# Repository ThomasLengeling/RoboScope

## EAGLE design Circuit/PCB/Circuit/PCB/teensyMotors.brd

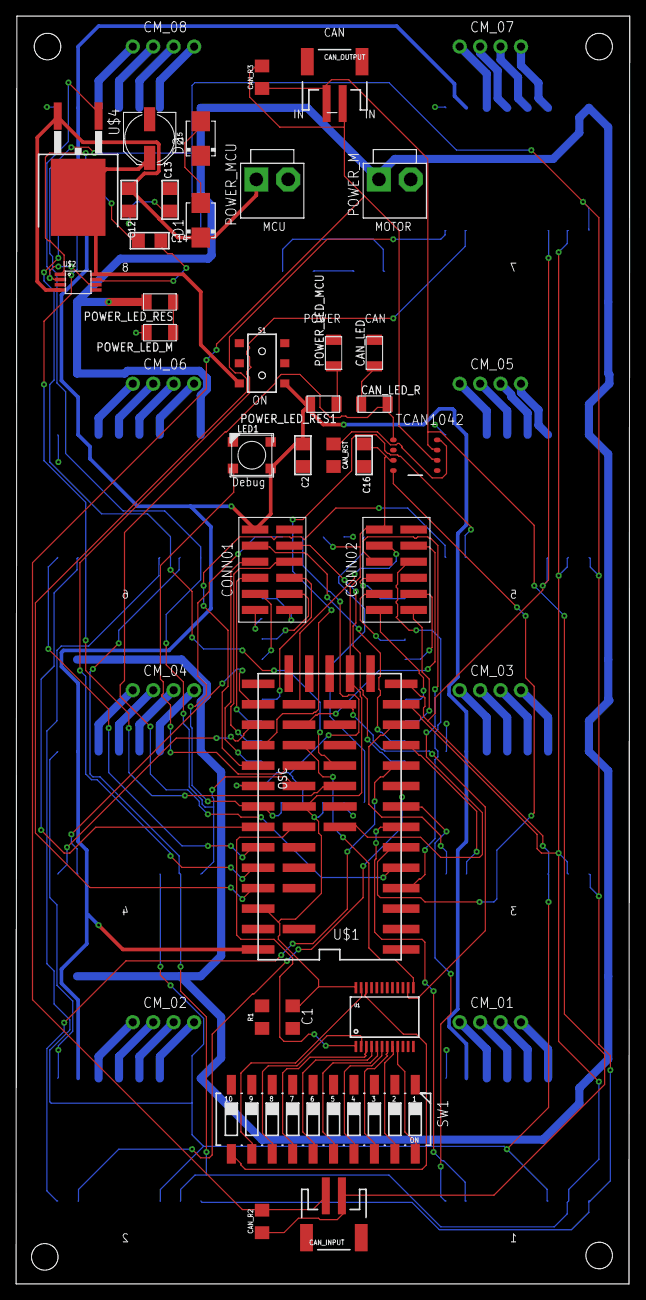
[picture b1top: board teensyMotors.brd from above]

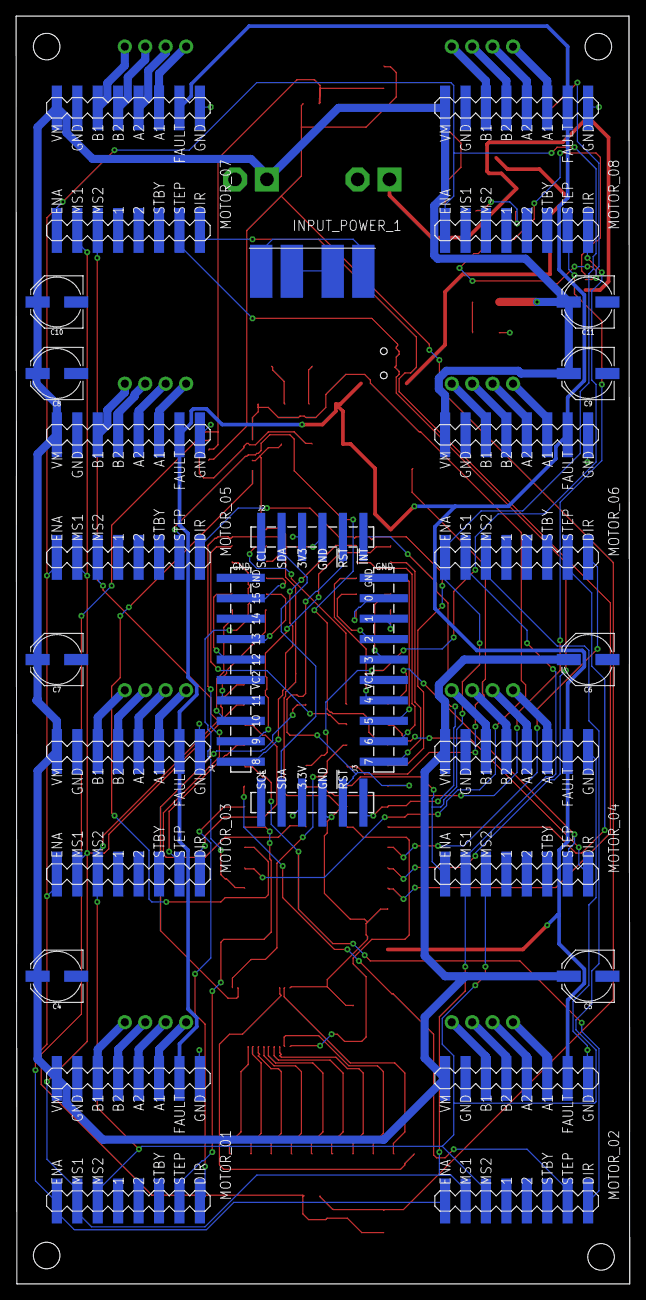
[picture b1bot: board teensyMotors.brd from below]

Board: 2 copper layers, 76.3 x 157.6 mm, 66 parts (21 on the bottom side), 109 nets.

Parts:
C1: 0.1uF; C1206
C2, C12, C13, C14, C16: 1206
C4, C5, C6, C7, C8, C9, C10, C11, C15: 100uF; PANASONIC_D
CAN_INPUT: JST-2-SMD
CAN_LED: LEDFAB1206; LED1206FAB
CAN_LED_R: 500; R1206FAB
CAN_OUTPUT: JST-2-SMD
CAN_R2, CAN_R3: 120ohm; 1206
CAN_RST: 10K; 1206
CM_01, CM_02, CM_03, CM_04, CM_05, CM_06, CM_07, CM_08: 1X04_SMD_STRAIGHT_COMBO; 1X04-CLEANBIG
CONN01, CONN02: TMMH-105-12
D1, D2: S2M; DO214AA
INPUT_POWER_1: MOLEX4015
J1, J2: 1X06_SMD_MALE
J3, J4: 1X10_SMD_MALE
LED1: LED5050_N
MOTOR_01, MOTOR_02, MOTOR_03, MOTOR_04, MOTOR_05, MOTOR_06, MOTOR_07, MOTOR_08: DRV8880
POWER_LED_M: LEDFAB1206; LED1206FAB
POWER_LED_MCU: LEDFAB1206; LED1206FAB
POWER_LED_RES, POWER_LED_RES1: 500; R1206FAB
POWER_M: B2P-VH
POWER_MCU: B2P-VH
R1: 1206
S1: SWITCH_DPDT_SMD_AYZ0202
STANDOFF5, STANDOFF6, STANDOFF7, STANDOFF8: STAND-OFF
SW1: 219-10; CTS-219-10
TCAN1042: Value; D0008A_N
U1: MUX-74HC4067; SSOP24
U$1: TEENSY_3.1-3.2_ALL_PINS&PADS_SMD; TEENSY_3.0-3.2_ALL_PINS_&_PADS_SMD
U$2: VSSOP(8)
U$4: TO263-3

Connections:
3.3V: C1.1, C16.1, CONN02.11, J1.4, J2.4, TCAN1042.3, U1.24, U$1.3.3V, U$1.3.3V1, U$1.3.3V2
C0: SW1.20, U1.9
C1: SW1.19, U1.8
C2: SW1.18, U1.7
C3: SW1.17, U1.6
C4: SW1.16, U1.5
C5: SW1.15, U1.4
C6: SW1.14, U1.3
C7: SW1.13, U1.2
C8: SW1.12, U1.23
C9: SW1.11, U1.22
CAN_H: CAN_INPUT.1, CAN_OUTPUT.1, CAN_R2.1, CAN_R3.1, TCAN1042.7
CAN_L: CAN_INPUT.2, CAN_OUTPUT.2, CAN_R2.2, CAN_R3.2, TCAN1042.6
CAN_RX: TCAN1042.4, U$1.4
CAN_TX: CAN_LED_R.2, TCAN1042.1, U$1.3
GND_IN: INPUT_POWER_1.GND_01, INPUT_POWER_1.GND_02
GND_M: C4.-, C5.-, C6.-, C7.-, C8.-, C9.-, C10.-, C11.-, MOTOR_01.GND_1, MOTOR_02.GND_1, MOTOR_03.GND_1, MOTOR_04.GND_1, MOTOR_05.GND_1, MOTOR_06.GND_1, MOTOR_07.GND_1, MOTOR_08.GND_1, POWER_LED_M.2, POWER_M.2
GND_MCU: C1.2, C2.2, C13.2, C15.-, C16.2, CAN_LED.2, CAN_RST.2, CONN01.12, CONN02.12, D2.C, J1.3, J2.3, LED1.3-GND, MOTOR_01.GND_0, MOTOR_02.GND_0, MOTOR_03.GND_0, MOTOR_04.GND_0, MOTOR_05.GND_0, MOTOR_06.GND_0, MOTOR_07.GND_0, MOTOR_08.GND_0, POWER_LED_MCU.2, POWER_MCU.2, R1.1, R1.2, SW1.1, SW1.2, SW1.3, SW1.4, SW1.5, SW1.6, SW1.7, SW1.8, SW1.9, SW1.10, TCAN1042.2, U1.12, U1.15, U$1.GND, U$1.GND1, U$1.GND2
I2CM_0: CONN01.1, J3.9
I2CM_1: CONN01.2, J3.8
I2CM_2: CONN01.3, J3.7
I2CM_3: CONN01.4, J3.6
I2CM_4: CONN01.5, J3.4
I2CM_5: CONN01.6, J3.3
I2CM_6: CONN01.7, J3.2
I2CM_7: CONN01.8, J3.1
I2CM_8: CONN01.9, J4.1
I2CM_9: CONN01.10, J4.2
I2CM_10: CONN02.1, J4.3
I2CM_11: CONN02.2, J4.4
I2CM_12: CONN02.3, J4.6
I2CM_13: CONN02.4, J4.7
I2CM_15: CONN02.6, J4.9
LED_DEBUG: LED1.4-DIN, U$1.32
MA1_01: CM_01.1, MOTOR_01.A1
MA1_02: CM_02.1, MOTOR_02.A1
MA1_03: CM_03.1, MOTOR_03.A1
MA1_04: CM_04.1, MOTOR_04.A1
MA1_05: CM_05.1, MOTOR_05.A1
MA1_06: CM_06.1, MOTOR_06.A1
MA1_07: CM_07.1, MOTOR_07.A1
MA1_08: CM_08.1, MOTOR_08.A1
MA2_01: CM_01.2, MOTOR_01.A2
MA2_02: CM_02.2, MOTOR_02.A2
MA2_03: CM_03.2, MOTOR_03.A2
MA2_04: CM_04.2, MOTOR_04.A2
MA2_05: CM_05.2, MOTOR_05.A2
MA2_06: CM_06.2, MOTOR_06.A2
MA2_07: CM_07.2, MOTOR_07.A2
MA2_08: CM_08.2, MOTOR_08.A2
MB1_01: CM_01.4, MOTOR_01.B1
MB1_02: CM_02.4, MOTOR_02.B1
MB1_03: CM_03.4, MOTOR_03.B1
MB1_04: CM_04.4, MOTOR_04.B1
MB1_05: CM_05.4, MOTOR_05.B1
MB1_06: CM_06.4, MOTOR_06.B1
MB1_07: CM_07.4, MOTOR_07.B1
MB1_08: CM_08.4, MOTOR_08.B1
MB2_01: CM_01.3, MOTOR_01.B2
MB2_02: CM_02.3, MOTOR_02.B2
MB2_03: CM_03.3, MOTOR_03.B2
MB2_04: CM_04.3, MOTOR_04.B2
MB2_05: CM_05.3, MOTOR_05.B2
MB2_06: CM_06.3, MOTOR_06.B2
MB2_07: CM_07.3, MOTOR_07.B2
MB2_08: CM_08.3, MOTOR_08.B2
MDIR_01: MOTOR_01.DIR, U$1.6
MDIR_02: MOTOR_02.DIR, U$1.8
MDIR_03: MOTOR_03.DIR, U$1.10
MDIR_04: MOTOR_04.DIR, U$1.15/A1
MDIR_05: MOTOR_05.DIR, U$1.17/A3
MDIR_06: MOTOR_06.DIR, U$1.21/A7
MDIR_07: MOTOR_07.DIR, U$1.23/A9
MDIR_08: MOTOR_08.DIR, U$1.25
MENABLE: MOTOR_01.ENA, MOTOR_02.ENA, MOTOR_03.ENA, MOTOR_04.ENA, MOTOR_05.ENA, MOTOR_06.ENA, MOTOR_07.ENA, MOTOR_08.ENA, U$1.33
MMS1: MOTOR_01.MS1, MOTOR_02.MS1, MOTOR_03.MS1, MOTOR_04.MS1, MOTOR_05.MS1, MOTOR_06.MS1, MOTOR_07.MS1, U$1.11
MMS2: MOTOR_01.MS2, MOTOR_02.MS2, MOTOR_03.MS2, MOTOR_04.MS2, MOTOR_05.MS2, MOTOR_06.MS2, MOTOR_07.MS2, U$1.12
MSTEP_01: MOTOR_01.STEP, U$1.5
MSTEP_02: MOTOR_02.STEP, U$1.7
MSTEP_03: MOTOR_03.STEP, U$1.9
MSTEP_04: MOTOR_04.STEP, U$1.14/A0
MSTEP_05: MOTOR_05.STEP, U$1.16/A2
MSTEP_06: MOTOR_06.STEP, U$1.20/A6
MSTEP_07: MOTOR_07.STEP, U$1.22/A8
MSTEP_08: MOTOR_08.STEP, U$1.24
MUX_RESET: J1.2, J2.2
MUX_S2: U1.14, U$1.28
MUX_S3: U1.13, U$1.31
MUX_SCL: J1.6, J2.6, U$1.19/A5
MUX_SDA: J1.5, J2.5, U$1.18/A4
MUX_SIG: U1.1, U$1.A13
unnamed: POWER_LED_M.1, POWER_LED_RES.1
unnamed: C14.2, U$2.VCAPH
unnamed: U$2.GDRIVE, U$2.GPD, U$4.1
unnamed: C14.1, U$2.VCAPL
unnamed: CAN_RST.1, TCAN1042.8
unnamed: POWER_LED_MCU.1, POWER_LED_RES1.1
unnamed: C12.2, C13.1
unnamed: D1.A, D2.A
unnamed: CAN_LED.1, CAN_LED_R.1
NEO_PIXEL: CONN02.7, U$1.2
REG_5V: C15.+, S1.6, U$2.CATHODE, U$4.4
S_SCL: CONN02.10, U$1.29
S_SDA: CONN02.9, U$1.30
S_SEN_01: CONN02.8, U$1.A12
VCC_5V: C2.1, CONN01.11, LED1.1-VDD, MOTOR_01.FAULT, MOTOR_02.FAULT, MOTOR_03.FAULT, MOTOR_04.FAULT, MOTOR_05.FAULT, MOTOR_06.FAULT, MOTOR_07.FAULT, MOTOR_08.FAULT, POWER_LED_RES1.2, S1.3, U$1.VIN
VCC_IN: INPUT_POWER_1.VCC_01, INPUT_POWER_1.VCC_02
VCC_M: C4.+, C5.+, C6.+, C7.+, C8.+, C9.+, C10.+, C11.+, MOTOR_01.VM, MOTOR_02.VM, MOTOR_03.VM, MOTOR_04.VM, MOTOR_05.VM, MOTOR_06.VM, MOTOR_07.VM, MOTOR_08.VM, POWER_LED_RES.2, POWER_M.1
VCC_MCU: C12.1, D1.C, POWER_MCU.1, U$2.ANODE, U$4.3

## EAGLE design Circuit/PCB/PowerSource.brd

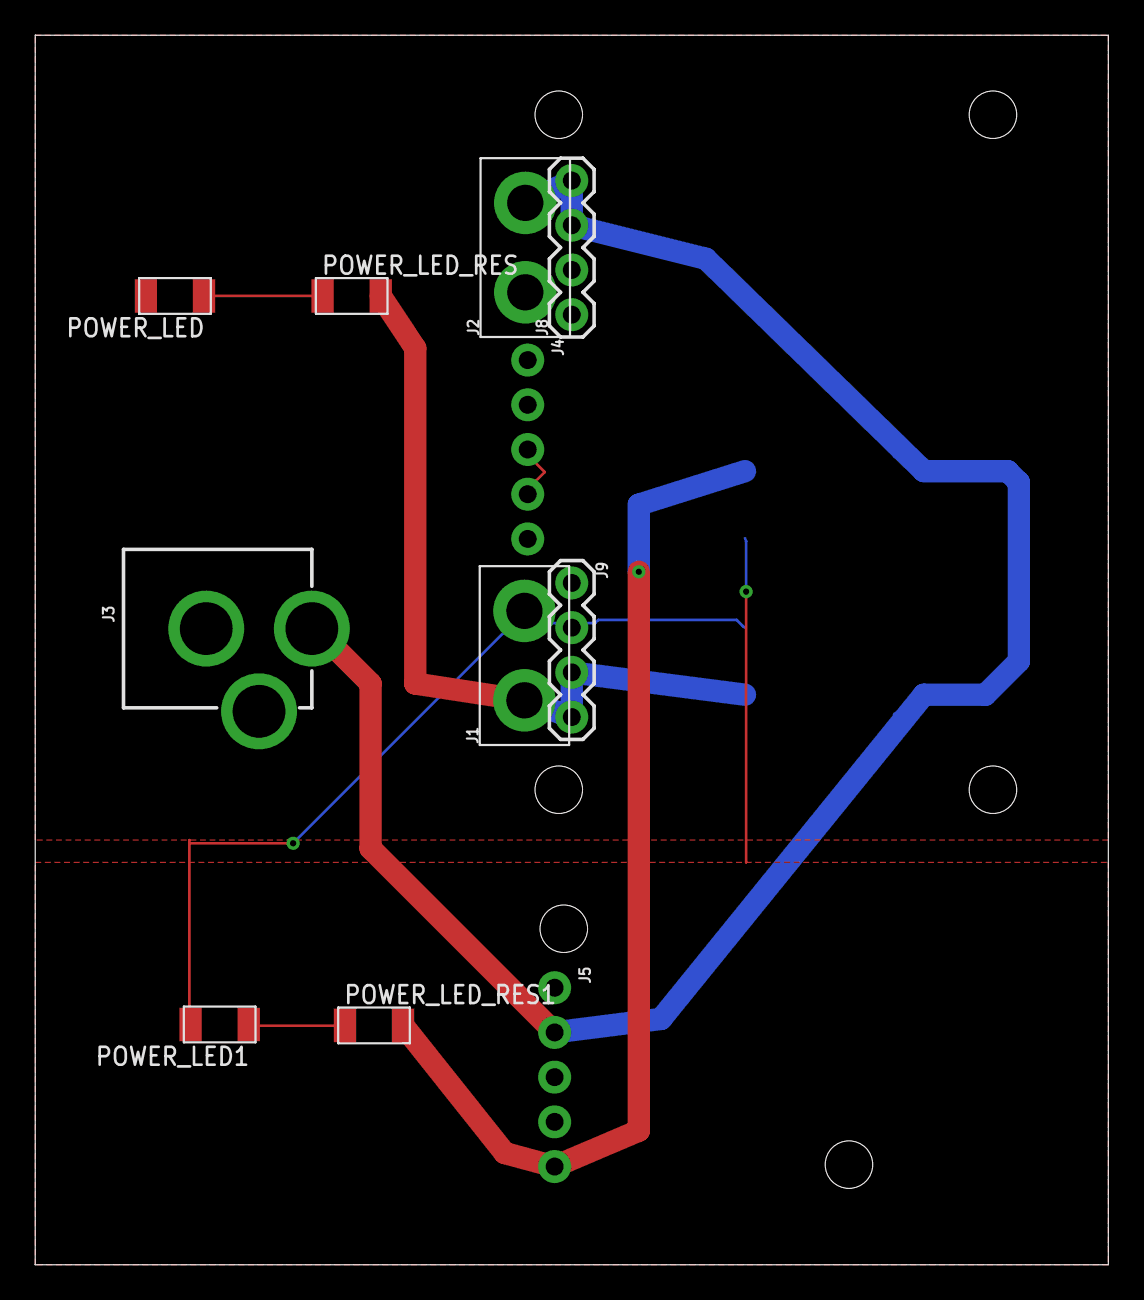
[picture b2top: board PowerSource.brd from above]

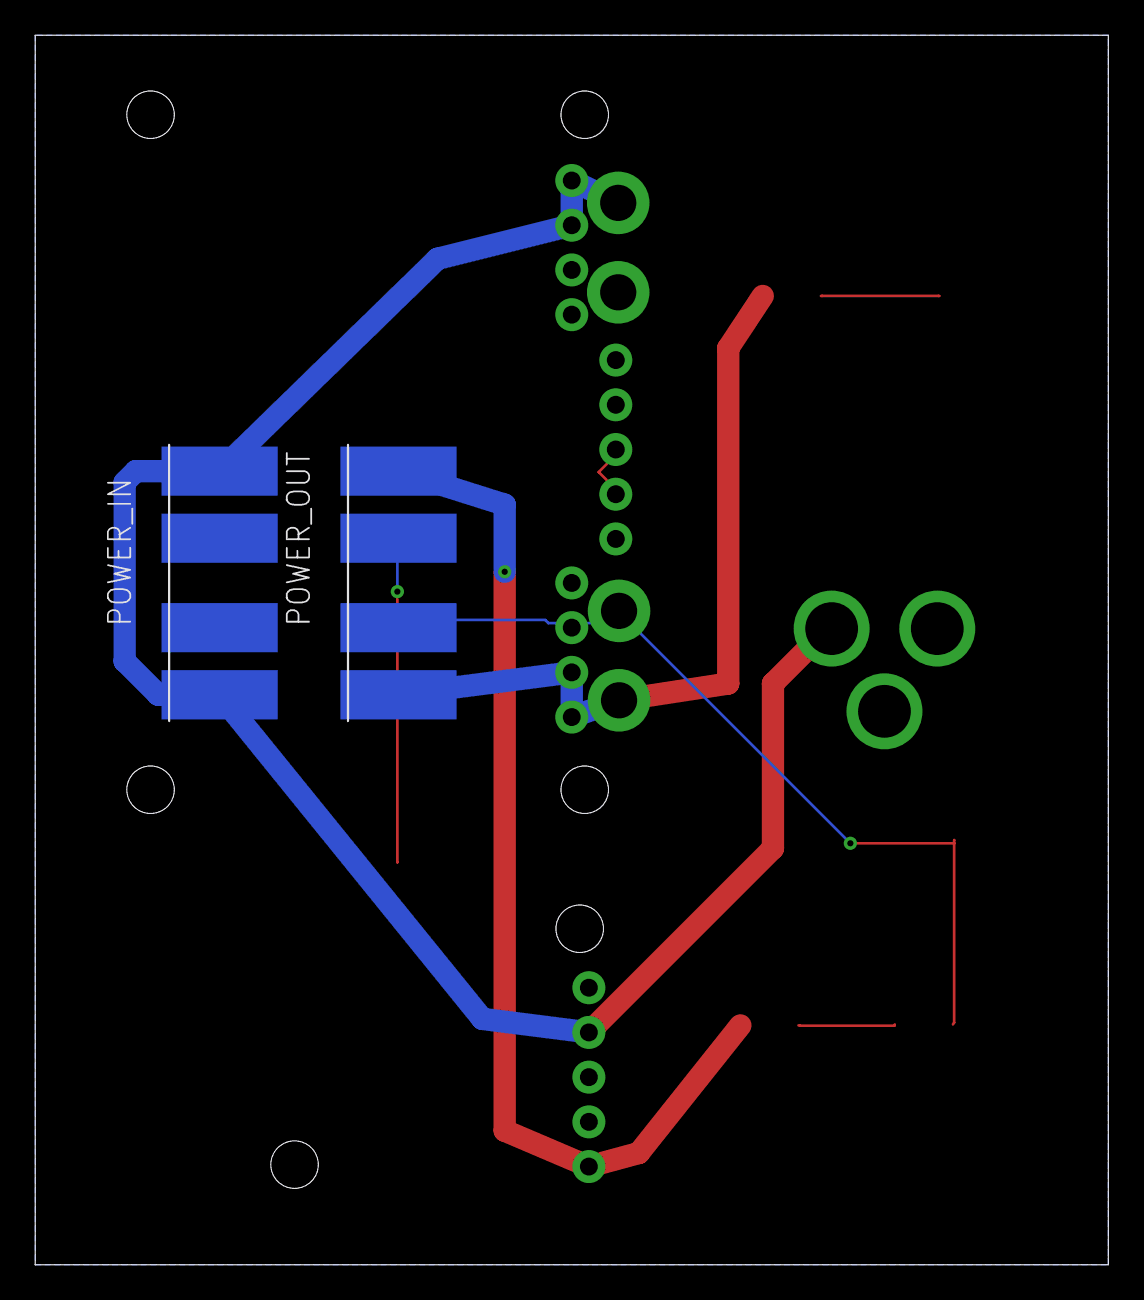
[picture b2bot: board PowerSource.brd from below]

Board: 2 copper layers, 61.0 x 69.8 mm, 13 parts (2 on the bottom side), 9 nets.

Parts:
J1, J2: 1X02_XTRA_BIG
J3: POWER_JACK; POWER_JACK_PTH
J4, J5: 1X05_NO_SILK
J8, J9: 1X04
POWER_IN: MOLEX4015
POWER_LED, POWER_LED1: LEDFAB1206; LED1206FAB
POWER_LED_RES, POWER_LED_RES1: 500; R1206FAB
POWER_OUT: MOLEX4015

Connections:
GND: J4.3, J4.4
GND_IN: J2.1, J3.GND, J3.GNDBREAK, J5.3, J8.1, J8.2, POWER_IN.GND_01, POWER_IN.GND_02
GND_M: J1.2, J9.1, J9.2, POWER_LED.2, POWER_LED1.2, POWER_OUT.GND_01
GND_MCU: J5.4, POWER_OUT.GND_02
unnamed: POWER_LED.1, POWER_LED_RES.1
unnamed: POWER_LED1.1, POWER_LED_RES1.1
VCC_IN: J2.2, J3.PWR, J5.2, J8.3, J8.4, POWER_IN.VCC_01, POWER_IN.VCC_02
VCC_M: J1.1, J9.3, J9.4, POWER_LED_RES.2, POWER_OUT.VCC_01
VCC_MCU: J5.5, POWER_LED_RES1.2, POWER_OUT.VCC_02

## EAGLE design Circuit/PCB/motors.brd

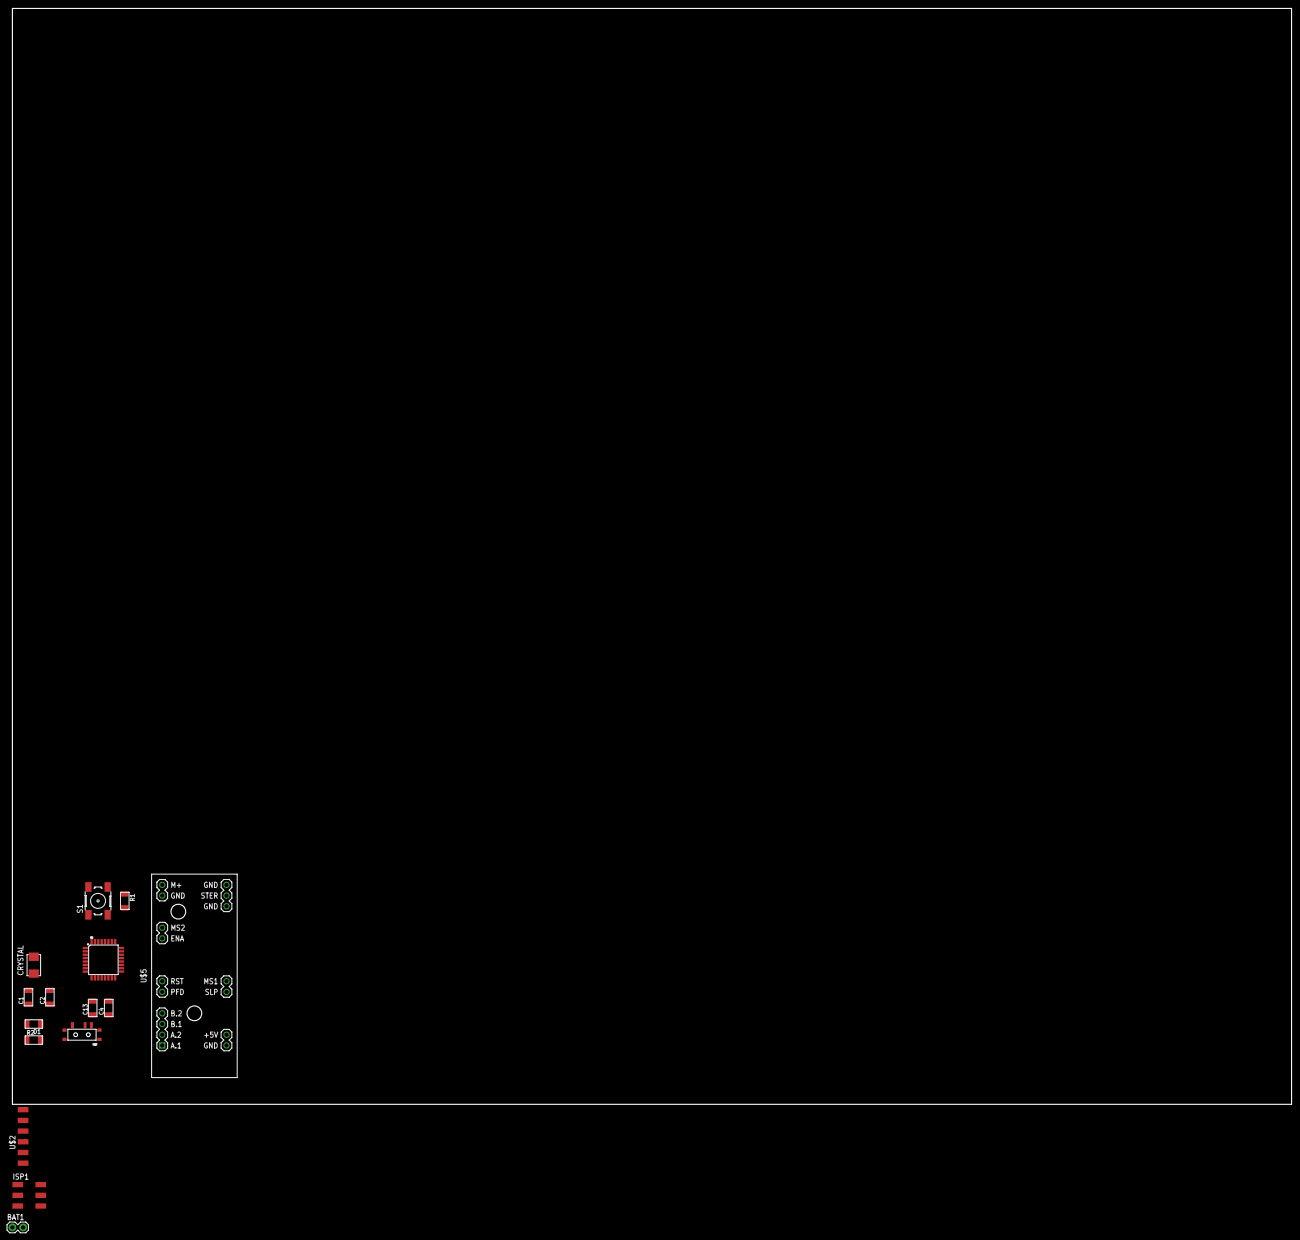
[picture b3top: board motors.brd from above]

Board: 2 copper layers, 303.5 x 260.0 mm, 15 parts (0 on the bottom side), 16 nets, no tracks yet.

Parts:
BAT1: 1X02
C1, C2: 22pF; C1206FAB
C4, C13: 0.1uF; C1206FAB
CRYSTAL: 16MHz; 2-SMD-5X3MM
D1: LEDFAB1206; LED1206FAB
ISP1: 2X03SMD
R1: 10k; R1206FAB
R2: 500; R1206FAB
S1: 6MM_SWITCH
U2: ATMEGA328P_TQFP; TQFP32-08
U$2: FTDI-SMD-HEADER; 1X06SMD
U$3: SWITCH_SPDT; KPS-1290
U$5: STEPPER-MOTOR-EASY-DRIVER

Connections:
5V: R1.2, U2.4, U2.6, U2.18
BAT_IN: BAT1.2, U$3.P
DTR: C4.1, U$2.6
GND: BAT1.1, C1.2, C2.2, C13.1, D1.2, ISP1.6, S1.1, S1.2, U2.3, U2.5, U2.21, U$2.1, U$2.2
MISO: ISP1.1, U2.16
MOSI: ISP1.4, U2.15
unnamed: D1.1, R2.1
unnamed: C13.2, U2.20
unnamed: R2.2, U2.1
RST: C4.2, ISP1.5, R1.1, S1.3, S1.4, U2.29
RX: U2.31, U$2.5
SCK: ISP1.3, U2.17
TX: U2.30, U$2.4
VBUS: ISP1.2, U$2.3
XTAL1: C1.1, CRYSTAL.P$1, U2.7
XTAL2: C2.1, CRYSTAL.P$2, U2.8

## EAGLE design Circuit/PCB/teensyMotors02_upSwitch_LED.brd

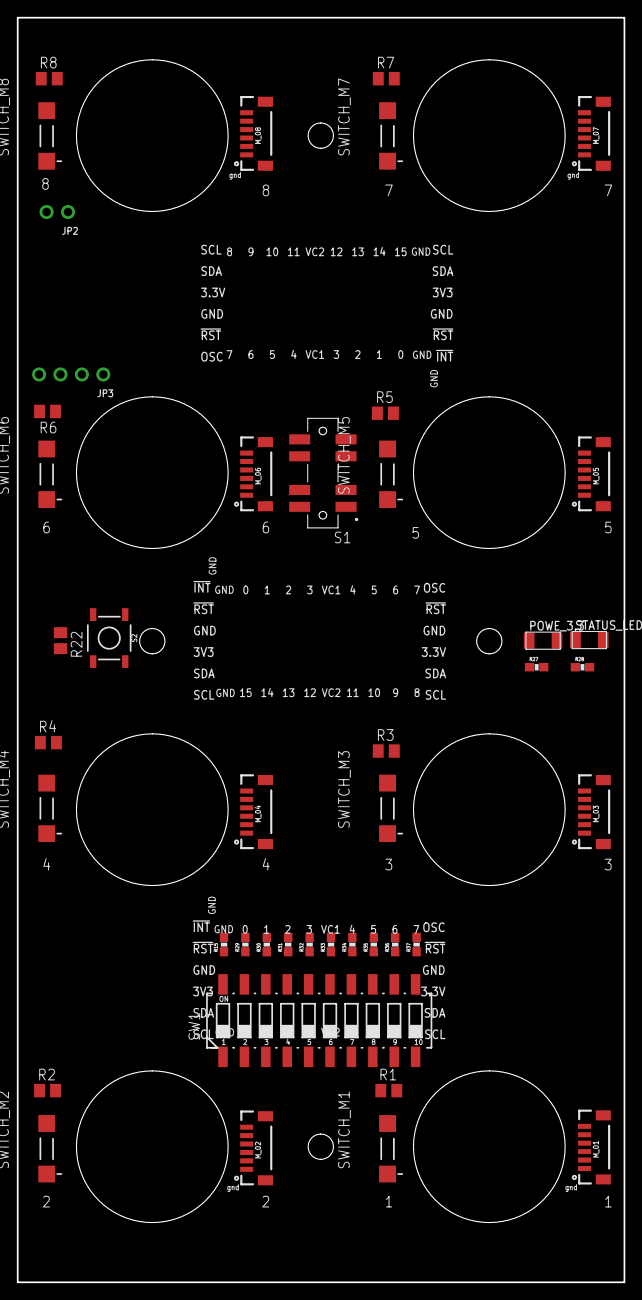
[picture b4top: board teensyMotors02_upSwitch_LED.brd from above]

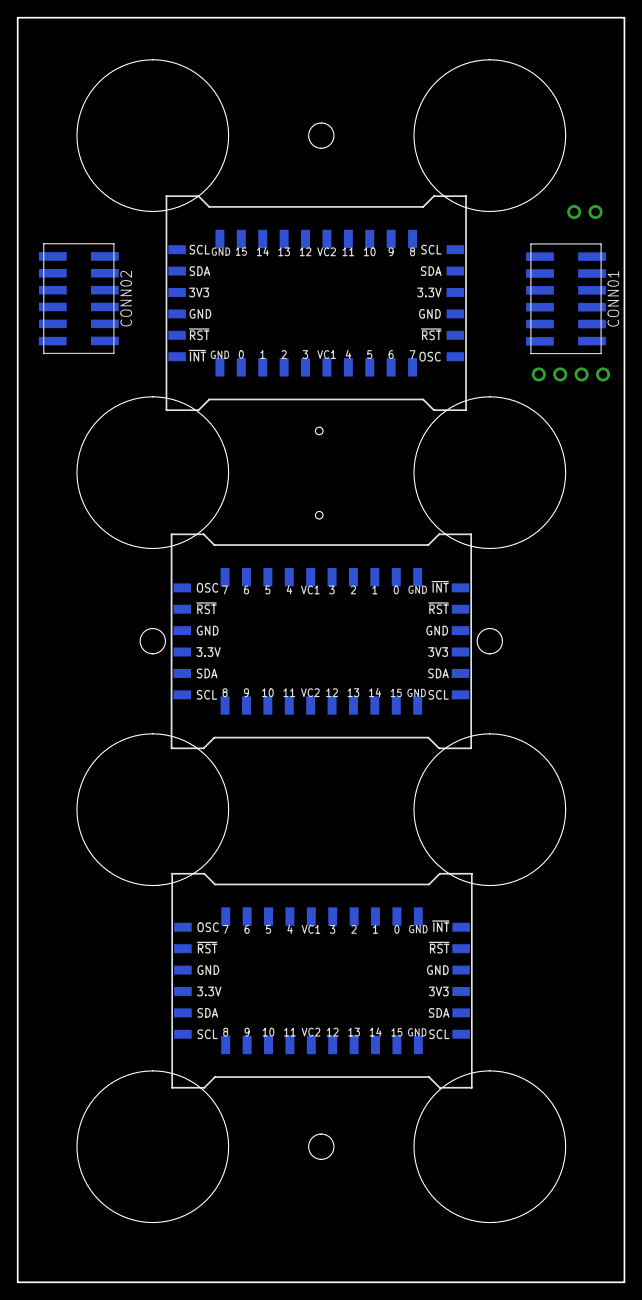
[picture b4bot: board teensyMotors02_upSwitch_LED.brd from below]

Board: 2 copper layers, 72.0 x 150.1 mm, 49 parts (5 on the bottom side), 66 nets, no tracks yet.

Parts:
CONN01, CONN02: TMMH-105-12
JP2: 1X02_ROUND
JP3: 1X04_ROUND
M_01, M_02, M_03, M_04, M_05, M_06, M_07, M_08: 1X06-1MM
POWE_3.3: LEDFAB1206; LED1206FAB
R1, R2, R3, R5, R6, R7, R8: 10k; M0805
R4, R22: 10K; M0805
R15, R29, R30, R31, R32, R33, R34, R35, R36, R37: 10K; 0603-RES
R27, R28: 500; 0603-RES
S1: JS207011SCQNR; SW_JS207011SCQNR
S2: TACTILE_SWITCH_SMD_5.2MM
STATUS_LED: LEDFAB1206; LED1206FAB
SW1: 219-10; CTS-219-10
SWITCH_M1, SWITCH_M2, SWITCH_M3, SWITCH_M4, SWITCH_M5, SWITCH_M6, SWITCH_M7, SWITCH_M8: DTSM-3
U$1, U$2, U$3: SX1509

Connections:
0_SX1: M_04.6, U$1.0
0_SX2: M_08.6, U$2.0
1_SX1: M_04.5, U$1.1
1_SX2: M_08.5, U$2.1
2_SX1: M_02.6, U$1.2
2_SX2: M_06.6, U$2.2
2_SX3: CONN01.8, U$3.2
3.3V: CONN01.10, CONN02.10, JP3.1, R15.2, R27.2, R29.2, R30.2, R31.2, R32.2, R33.2, R34.2, R35.2, R36.2, R37.2, S2.1, S2.2, SWITCH_M1.1, SWITCH_M2.1, SWITCH_M3.1, SWITCH_M4.1, SWITCH_M5.1, SWITCH_M6.1, SWITCH_M7.1, SWITCH_M8.1, U$1.3.3V, U$1.3.3V_1, U$2.3.3V, U$2.3.3V_1, U$3.3.3V, U$3.3.3V_1
3_SX1: M_02.5, U$1.3
3_SX2: M_06.5, U$2.3
3_SX3: CONN01.7, U$3.3
4_SX1: M_02.4, U$1.4
4_SX2: M_06.4, U$2.4
4_SX3: R22.2, S2.3, S2.4, U$3.4
5_SX1: M_04.4, U$1.5
5_SX2: M_08.4, U$2.5
5_SX3: R15.1, SW1.20, U$3.5
6_SX1: R2.2, SWITCH_M2.2, U$1.6
6_SX2: R6.2, SWITCH_M6.2, U$2.6
6_SX3: R29.1, SW1.19, U$3.6
7_SX1: R4.2, SWITCH_M4.2, U$1.7
7_SX2: R8.2, SWITCH_M8.2, U$2.7
7_SX3: R30.1, SW1.18, U$3.7
8_SX1: R1.2, SWITCH_M1.2, U$1.8
8_SX2: R5.2, SWITCH_M5.2, U$2.8
8_SX3: R31.1, SW1.17, U$3.8
9_SX1: R3.2, SWITCH_M3.2, U$1.9
9_SX2: R7.2, SWITCH_M7.2, U$2.9
9_SX3: R32.1, SW1.16, U$3.9
10_SX1: M_01.6, U$1.10
10_SX2: M_05.6, U$2.10
10_SX3: R33.1, SW1.15, U$3.10
11_SX1: M_01.5, U$1.11
11_SX2: M_05.5, U$2.11
11_SX3: R34.1, SW1.14, U$3.11
12_SX1: M_01.4, U$1.12
12_SX2: M_05.4, U$2.12
12_SX3: R35.1, SW1.13, U$3.12
13_SX1: M_03.6, U$1.13
13_SX2: M_07.6, U$2.13
13_SX3: R36.1, SW1.12, U$3.13
14_SX1: M_03.5, U$1.14
14_SX2: M_07.5, U$2.14
14_SX3: R37.1, SW1.11, U$3.14
15_SX1: M_03.4, U$1.15
15_SX2: M_07.4, U$2.15
15_SX3: R28.2, U$3.15
CAN_RX2: CONN01.4, JP3.4
CAN_TX2: CONN01.3, JP3.3
GND_MCU: CONN01.9, CONN01.11, CONN02.9, CONN02.11, JP3.2, M_01.1, M_02.1, M_03.1, M_04.1, M_05.1, M_06.1, M_07.1, M_08.1, POWE_3.3.2, R1.1, R2.1, R3.1, R4.1, R5.1, R6.1, R7.1, R8.1, R22.1, STATUS_LED.2, SW1.1, SW1.2, SW1.3, SW1.4, SW1.5, SW1.6, SW1.7, SW1.8, SW1.9, SW1.10, U$1.GND, U$1.GND_1, U$1.GND_2, U$1.GND_3, U$2.GND, U$2.GND_1, U$2.GND_2, U$2.GND_3, U$3.GND, U$3.GND_1, U$3.GND_2, U$3.GND_3
unnamed: R28.1, STATUS_LED.1
unnamed: POWE_3.3.1, R27.1
NEOPIXEL_01: CONN02.2, M_01.3
NEOPIXEL_02: CONN02.1, M_02.3
NEOPIXEL_03: CONN02.4, M_03.3
NEOPIXEL_04: CONN02.3, M_04.3
NEOPIXEL_05: CONN02.6, M_05.3
NEOPIXEL_06: CONN02.5, M_06.3
NEOPIXEL_07: CONN02.8, M_07.3
NEOPIXEL_08: CONN02.7, M_08.3
RX7: CONN01.6, JP2.2
SCL_00: CONN01.2, U$1.SCL, U$1.SCL_2, U$1.SDA, U$1.SDA_2, U$2.SCL, U$2.SCL_2, U$3.SCL, U$3.SCL_2
SDA_00: CONN01.1, U$2.SDA, U$2.SDA_2, U$3.SDA, U$3.SDA_2
TX7: CONN01.5, JP2.1
VCC_5V: M_01.2, M_02.2, M_03.2, M_04.2, M_05.2, M_06.2, M_07.2, M_08.2, S1.2
VCC_5V_IN: CONN01.12, CONN02.12, S1.3

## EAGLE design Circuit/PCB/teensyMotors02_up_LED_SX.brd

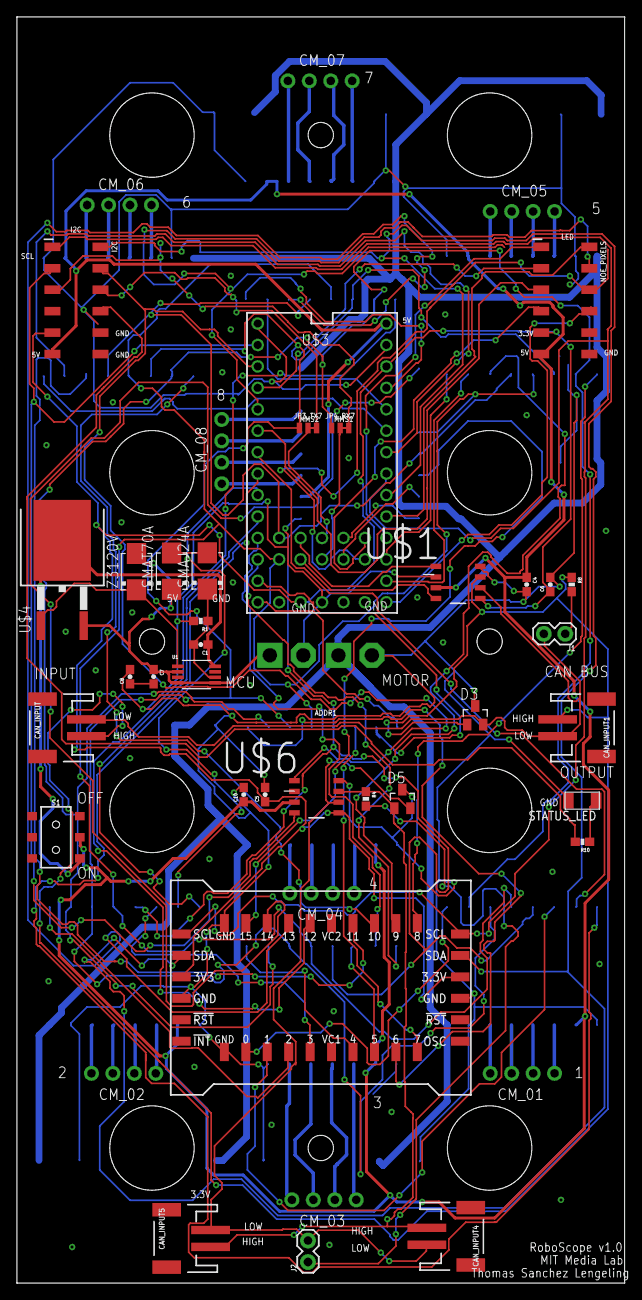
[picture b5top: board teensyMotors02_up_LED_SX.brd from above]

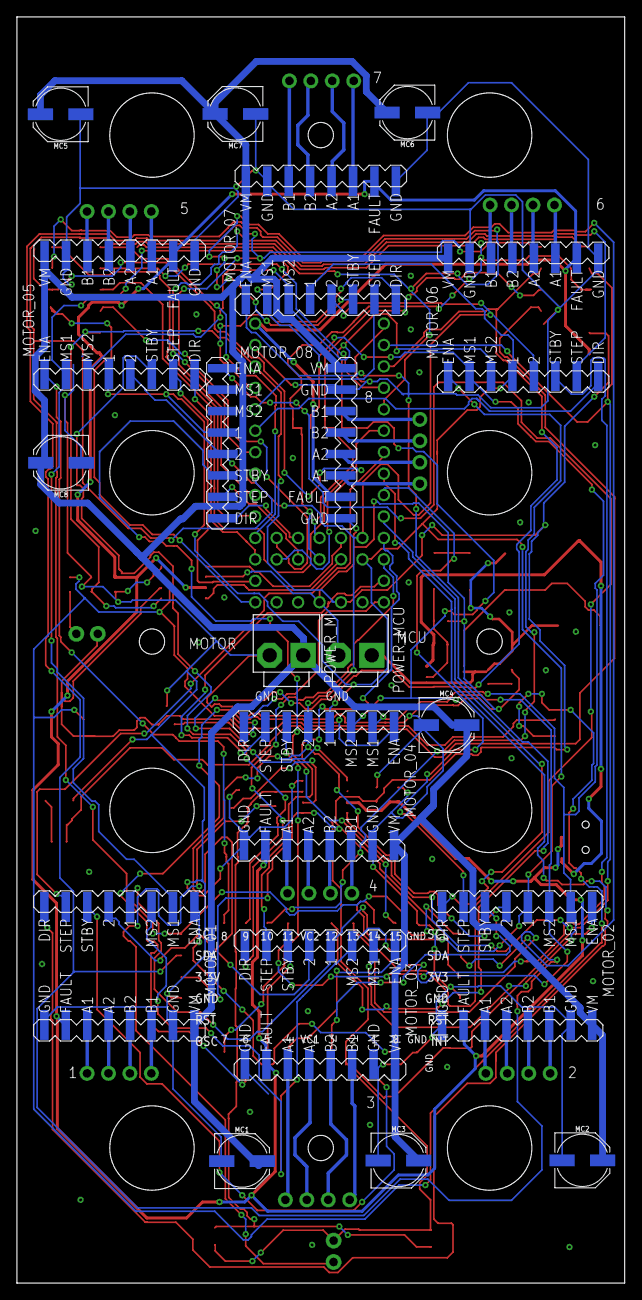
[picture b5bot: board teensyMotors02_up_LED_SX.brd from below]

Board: 2 copper layers, 72.0 x 150.0 mm, 60 parts (18 on the bottom side), 104 nets.

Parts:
C1: 1.5uf; 0603-CAP
C4, C5, C6, C7, C8, C10: 0.1uf; 0603-CAP
CAN_INPUT, CAN_INPUT1, CAN_INPUT4, CAN_INPUT5: JST-2-SMD
CM_01, CM_02, CM_03, CM_04, CM_05, CM_06, CM_07, CM_08: 1X04_STRAIGHT; 1X04-CLEANBIG
D3, D5: PESD1CAN; SOT23
I2C: 2X6_SMD
J1, J2: 1X02
JP3_TX7, JP4_RX7: JUMPER-SMT_3_1-NC_TRACE_NO-SILK; SMT-JUMPER_3_1-NC_TRACE_NO-SILK
MC1, MC2, MC3, MC4, MC5, MC6, MC7, MC8: 100uF; PANASONIC_D
MOTOR_01, MOTOR_02, MOTOR_03, MOTOR_04, MOTOR_05, MOTOR_06, MOTOR_07, MOTOR_08: DRV8880
NOE_PIXELS: 2X6_SMD
POWER_M: B2P-VH
POWER_MCU: B2P-VH
R1: 1K; 0603-RES
R4, R8: 120Ohms; 0603-RES
R10: 500; 0603-RES
S1: SWITCH_DPDT_SMD_AYZ0202
SMAJ24A: S2M; DO214AA
SMAT70A: S2M; DO214AA
STATUS_LED: LEDFAB1206; LED1206FAB
U1: LTC4359CMS8PBF; MSOP-8_MS
U$1, U$6: MCP2562
U$3: TEENSY_4.0_WITH_SMD_HEADER_PINS
U$4: TO263-3
U$5: SX1509
Z3120V: S2M; DO214AA

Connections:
0_SX0: MOTOR_01.ENA, U$5.0
1_SX0: MOTOR_01.STBY, U$5.1
2_SX0: MOTOR_02.ENA, U$5.2
3.3V: C5.1, C6.1, I2C.9, NOE_PIXELS.9, U$1.VIO, U$3.3.3V, U$3.3.3V1, U$5.3.3V, U$5.3.3V_1, U$6.VIO
3_SX0: MOTOR_02.STBY, U$5.3
4_SX0: MOTOR_03.ENA, U$5.4
5_SX0: MOTOR_03.STBY, U$5.5
6_SX0: MOTOR_04.ENA, U$5.6
7_SX0: MOTOR_04.STBY, U$5.7
8_SX0: MOTOR_05.ENA, U$5.8
9_SX0: MOTOR_05.STBY, U$5.9
10_SX0: MOTOR_06.ENA, U$5.10
11_SX0: MOTOR_06.STBY, U$5.11
12_SX0: MOTOR_07.ENA, U$5.12
13_SX0: MOTOR_07.STBY, U$5.13
14_SX0: MOTOR_08.ENA, U$5.14
15_SX0: MOTOR_08.STBY, U$5.15
28_INT_01: JP4_RX7.2, U$3.28
29_INT_02: JP3_TX7.2, U$3.29
CAN_H: CAN_INPUT.1, CAN_INPUT1.1, D3.1, R8.1, U$1.CANH
CAN_H2: CAN_INPUT4.1, CAN_INPUT5.1, D5.1, R4.1, U$6.CANH
CAN_L: CAN_INPUT.2, CAN_INPUT1.2, D3.2, J1.2, U$1.CANL
CAN_L2: CAN_INPUT4.2, CAN_INPUT5.2, D5.2, J2.2, U$6.CANL
CAN_RX2: I2C.3, U$3.0, U$6.RXD
CAN_RX3: U$1.RXD, U$3.30
CAN_TX2: I2C.4, U$3.1, U$6.TXD
CAN_TX3: U$1.TXD, U$3.31
GND_MCU: C4.2, C5.2, C6.2, C8.2, C10.2, D3.3, D5.3, I2C.10, I2C.12, MC1.-, MC2.-, MC3.-, MC4.-, MC5.-, MC6.-, MC7.-, MC8.-, MOTOR_01.GND_0, MOTOR_01.GND_1, MOTOR_02.GND_0, MOTOR_02.GND_1, MOTOR_03.GND_0, MOTOR_03.GND_1, MOTOR_04.GND_0, MOTOR_04.GND_1, MOTOR_05.GND_0, MOTOR_05.GND_1, MOTOR_06.GND_0, MOTOR_06.GND_1, MOTOR_07.GND_0, MOTOR_07.GND_1, MOTOR_08.GND_0, MOTOR_08.GND_1, NOE_PIXELS.10, NOE_PIXELS.12, POWER_M.2, POWER_MCU.2, R1.2, STATUS_LED.2, U$1.STBY, U$1.VSS, U$3.GND, U$3.GND1, U$3.GND2, U$5.GND, U$5.GND_1, U$5.GND_2, U$5.GND_3, U$6.STBY, U$6.VSS
INT_01: I2C.5, JP4_RX7.3
INT_02: I2C.6, JP3_TX7.3
MA1_01: CM_01.1, MOTOR_01.A1
MA1_02: CM_02.1, MOTOR_02.A1
MA1_03: CM_03.1, MOTOR_03.A1
MA1_04: CM_04.1, MOTOR_04.A1
MA1_05: CM_05.1, MOTOR_05.A1
MA1_06: CM_06.1, MOTOR_06.A1
MA1_07: CM_07.1, MOTOR_07.A1
MA1_08: CM_08.1, MOTOR_08.A1
MA2_01: CM_01.2, MOTOR_01.A2
MA2_02: CM_02.2, MOTOR_02.A2
MA2_03: CM_03.2, MOTOR_03.A2
MA2_04: CM_04.2, MOTOR_04.A2
MA2_05: CM_05.2, MOTOR_05.A2
MA2_06: CM_06.2, MOTOR_06.A2
MA2_07: CM_07.2, MOTOR_07.A2
MA2_08: CM_08.2, MOTOR_08.A2
MB1_01: CM_01.4, MOTOR_01.B1
MB1_02: CM_02.4, MOTOR_02.B1
MB1_03: CM_03.4, MOTOR_03.B1
MB1_04: CM_04.4, MOTOR_04.B1
MB1_05: CM_05.4, MOTOR_05.B1
MB1_06: CM_06.4, MOTOR_06.B1
MB1_07: CM_07.4, MOTOR_07.B1
MB1_08: CM_08.4, MOTOR_08.B1
MB2_01: CM_01.3, MOTOR_01.B2
MB2_02: CM_02.3, MOTOR_02.B2
MB2_03: CM_03.3, MOTOR_03.B2
MB2_04: CM_04.3, MOTOR_04.B2
MB2_05: CM_05.3, MOTOR_05.B2
MB2_06: CM_06.3, MOTOR_06.B2
MB2_07: CM_07.3, MOTOR_07.B2
MB2_08: CM_08.3, MOTOR_08.B2
MDIR_01: MOTOR_01.DIR, U$3.6
MDIR_02: MOTOR_02.DIR, U$3.8
MDIR_03: MOTOR_03.DIR, U$3.10
MDIR_04: MOTOR_04.DIR, U$3.12
MDIR_05: MOTOR_05.DIR, U$3.15/A1
MDIR_06: MOTOR_06.DIR, U$3.21/A7
MDIR_07: MOTOR_07.DIR, U$3.23/A9
MDIR_08: MOTOR_08.DIR, U$3.27
MMS1: JP4_RX7.1, MOTOR_01.MS1, MOTOR_02.MS1, MOTOR_03.MS1, MOTOR_04.MS1, MOTOR_05.MS1, MOTOR_06.MS1, MOTOR_07.MS1
MMS2: JP3_TX7.1, MOTOR_01.MS2, MOTOR_02.MS2, MOTOR_03.MS2, MOTOR_04.MS2, MOTOR_05.MS2, MOTOR_06.MS2, MOTOR_07.MS2
MSTEP_01: MOTOR_01.STEP, U$3.5
MSTEP_02: MOTOR_02.STEP, U$3.7
MSTEP_03: MOTOR_03.STEP, U$3.9
MSTEP_04: MOTOR_04.STEP, U$3.11
MSTEP_05: MOTOR_05.STEP, U$3.14/A0
MSTEP_06: MOTOR_06.STEP, U$3.20/A6
MSTEP_07: MOTOR_07.STEP, U$3.22/A8
MSTEP_08: MOTOR_08.STEP, U$3.26
unnamed: J1.1, R8.2
unnamed: U1.1, U$4.1, Z3120V.C
unnamed: J2.1, R4.2
unnamed: C1.2, R1.1, SMAJ24A.C, U1.6
unnamed: C7.2, C8.1
unnamed: SMAJ24A.A, SMAT70A.A
unnamed: R10.1, STATUS_LED.1
NEOPIXEL_01: NOE_PIXELS.1, U$3.16/A2
NEOPIXEL_02: NOE_PIXELS.2, U$3.17/A3
NEOPIXEL_03: NOE_PIXELS.3, U$3.2
NEOPIXEL_04: NOE_PIXELS.4, U$3.3
NEOPIXEL_05: NOE_PIXELS.5, U$3.4
NEOPIXEL_06: NOE_PIXELS.6, U$3.24
NEOPIXEL_07: NOE_PIXELS.7, U$3.25
NEOPIXEL_08: NOE_PIXELS.8, U$3.13
REG_5V: C1.1, S1.3, U1.8, U$4.4
SCL_00: I2C.1, U$3.19/A5, U$5.SCL, U$5.SCL_2
SDA_00: I2C.2, U$3.18/A4, U$5.SDA, U$5.SDA_2
STATUS_PIN: I2C.8, R10.2
TRQ1: MOTOR_01.1, MOTOR_02.1, MOTOR_03.1, MOTOR_04.1, MOTOR_05.1, MOTOR_06.1, MOTOR_07.1, MOTOR_08.1, U$3.32
TRQ2: MOTOR_01.2, MOTOR_02.2, MOTOR_03.2, MOTOR_04.2, MOTOR_05.2, MOTOR_06.2, MOTOR_07.2, MOTOR_08.2, U$3.33
VCC_5V: C4.1, C10.1, I2C.11, MOTOR_01.FAULT, MOTOR_02.FAULT, MOTOR_03.FAULT, MOTOR_04.FAULT, MOTOR_05.FAULT, MOTOR_06.FAULT, MOTOR_07.FAULT, MOTOR_08.FAULT, NOE_PIXELS.11, S1.2, U$1.VDD, U$3.VIN, U$6.VDD
VCC_M: MC1.+, MC2.+, MC3.+, MC4.+, MC5.+, MC6.+, MC7.+, MC8.+, MOTOR_01.VM, MOTOR_02.VM, MOTOR_03.VM, MOTOR_04.VM, MOTOR_05.VM, MOTOR_06.VM, MOTOR_07.VM, MOTOR_08.VM, POWER_M.1
VCC_MCU: C7.1, POWER_MCU.1, SMAT70A.C, U1.2, U1.4, U1.5, U$4.3, Z3120V.A

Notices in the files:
parts and their libraries:
SparkFun-Electromechanical: Licensing: Creative Commons ShareAlike 4.0 International - https://creativecommons.org/licenses/by-sa/4.0
microbuilder: This work is placed in the public domain, and may be freely used for commercial and non-commercial work with the following conditions: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
